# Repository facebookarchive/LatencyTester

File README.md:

Latency Tester
==============

Firmware, Schematics, and Mechanicals for the Oculus Latency Tester.

https://www.oculusvr.com/order/latency-tester/

Firmware
--------

The Latency Tester firmware uses the CooCox CoIDE for development along with 
the gcc-arm-embedded toolchain.

The ST-Link/V2 is the cheapest way to load firmware onto a Latency Tester
board, though any SWD compatible programmer should work.  You can follow these steps
to set up a build environment and load firmware onto the board:

1. Install ST-Link drivers if you haven't: http://www.st.com/web/en/catalog/tools/PF258167
2. Install CoCenter: http://www.coocox.org/CooCox_CoIDE.htm
3. Through CoCenter, install CooCox and CoFlash
4. Install gcc-arm-embedded: https://launchpad.net/gcc-arm-embedded/+download
5. Set up gcc-arm-embedded in CooCox: http://www.coocox.org/CoIDE/Compiler_Settings.html
6. Clone our LatencyTester repository to C:\CooCox\CoIDE\workspace
7. Open the LatencyTester.coproj
8. Build
9. Plug the ST-Link into the board's 10 pin SWD header.
10. Plug in USB to power the board.
12. Download code to Flash 
13. Enjoy!

Note that the USB Product ID is set to 0x0101, which matches the production
version of the Latency Tester.  If you modify the firmware in a way that
changes the USB interface, please change the Product ID to 0x0100.

Mechanical
----------

The Mechanical folder contains STLs of a version of the Latency Tester housing
that is printable on low cost 3D printers as well as STEP files of the original
injection molded housing.

Schematics
----------

The Schematics folder contains an image of the schematic, as well as Eagle CAD files
of the schematic and board layout.

You can also order PCBs directly from OSH Park:

* Main PCB: http://oshpark.com/shared_projects/SHWtp0zm
* Sensor PCB: http://oshpark.com/shared_projects/nyOrdIp9

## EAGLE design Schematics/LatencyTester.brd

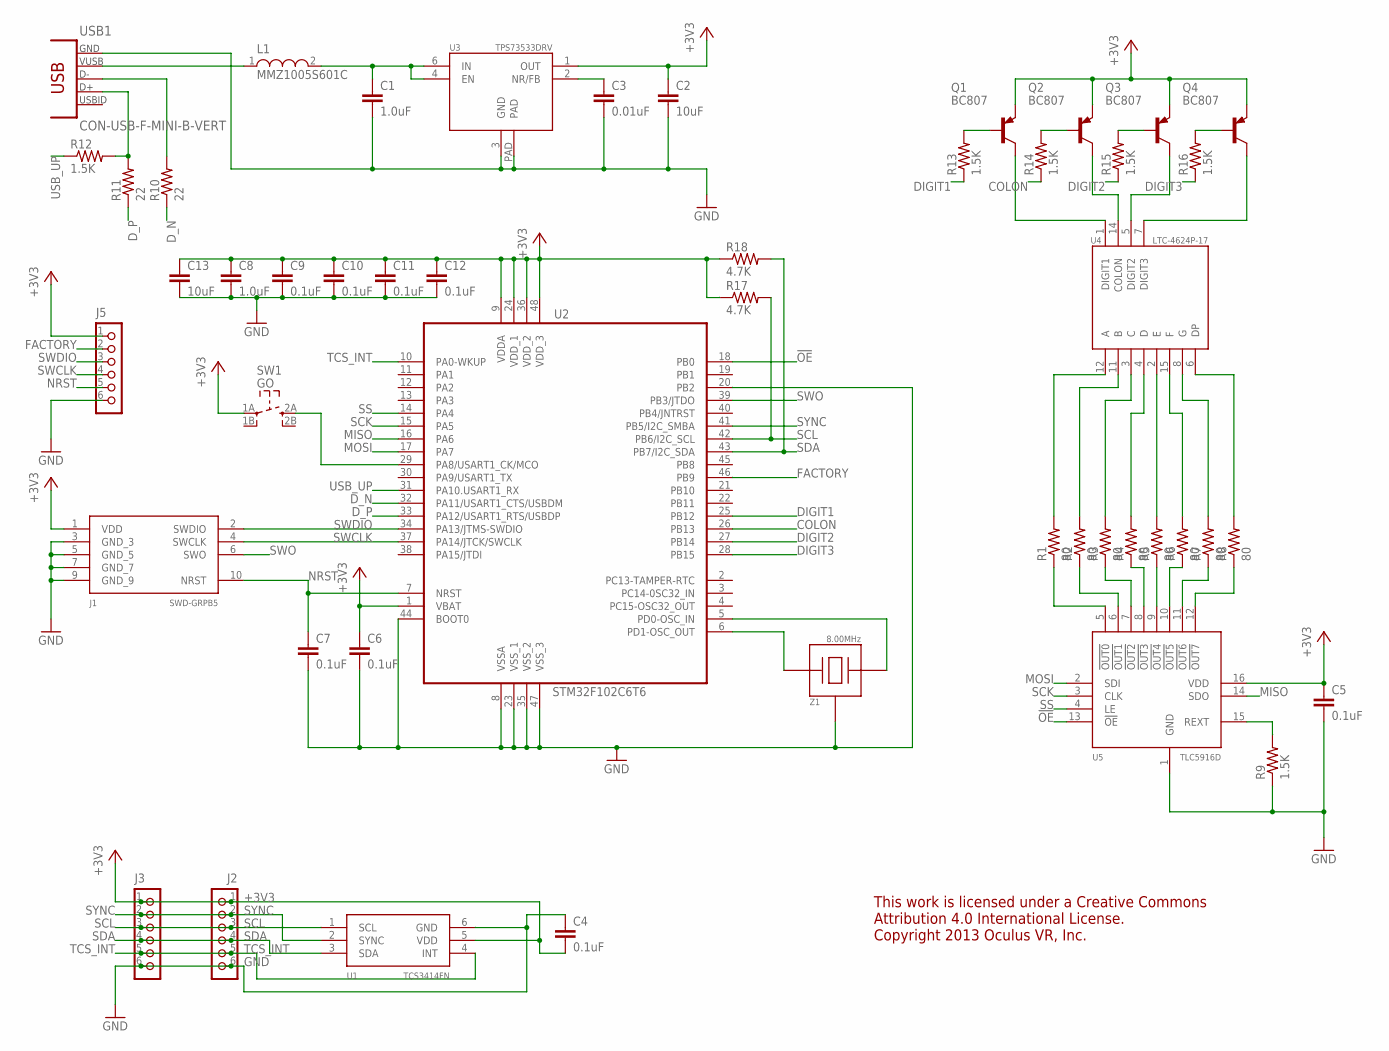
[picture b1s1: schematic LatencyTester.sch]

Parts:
C1, C8: 1.0uF; C0402
C2, C13: 10uF; C0805
C3: 0.01uF; C0402
C4, C5, C6, C7, C9, C10, C11, C12: 0.1uF; C0402
J1: SWD-GRPB5; GRPB5
J2, J3, J5: CON_HEADER_1X06-PTH; M1X6
L1: MMZ1005S601C; C402
Q1, Q2, Q3, Q4: BC807; SOT-323
R1, R2, R3, R4, R5, R6, R7, R8: 80; R0402
R9, R12, R13, R14, R15, R16: 1.5K; R0402
R10, R11: 22; R0402
R17, R18: 4.7K; R0402
SW1: GO; ADTS2
U1: TCS3414FN
U2: STM32F102C6T6; LQFP48
U3: TPS73533DRV; SON-6
U4: LTC-4624P-17; LTC-4624
U5: TLC5916D; SOIC-16
USB1: CON-USB-F-MINI-B-VERT; 651005136421
Z1: 8.00MHz; PQRV

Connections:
!OE: U2.18 (PB0), U5.13 (!OE)
+3V3: C2.1, C4.2, C5.1, C6.1, C8.1, C9.1, C10.1, C11.1, C12.1, C13.1, J1.1 (VDD), J2.1, J3.1, J5.1, Q1.2 (E), Q2.2 (E), Q3.2 (E), Q4.2 (E), R17.1, R18.1, SW1.1A (1), U1.5 (VDD), U2.1 (VBAT), U2.9 (VDDA), U2.24 (VDD_1), U2.36 (VDD_2), U2.48 (VDD_3), U3.1 (OUT), U5.16 (VDD)
COLON: R14.1, U2.26 (PB13)
D1_N: R10.2, USB1.2 (D-)
D1_P: R11.2, R12.2, USB1.3 (D+)
DIGIT1: R13.1, U2.25 (PB12)
DIGIT2: R15.1, U2.27 (PB14)
DIGIT3: R16.1, U2.28 (PB15)
D_N: R10.1, U2.32 (PA11/USART1_CTS/USBDM)
D_P: R11.1, U2.33 (PA12/USART1_RTS/USBDP)
FACTORY: J5.2, U2.46 (PB9)
GND: C1.2, C2.2, C3.2, C4.1, C5.2, C6.2, C7.2, C8.2, C9.2, C10.2, C11.2, C12.2, C13.2, J1.3 (GND_3), J1.5 (GND_5), J1.7 (GND_7), J1.9 (GND_9), J2.6, J3.6, J5.6, R9.1, U1.6 (GND), U2.8 (VSSA), U2.20 (PB2), U2.23 (VSS_1), U2.35 (VSS_2), U2.44 (BOOT0), U2.47 (VSS_3), U3.3 (GND), U3.PAD, U5.1 (GND), USB1.5 (GND), Z1.2 (GND)
MISO: U2.16 (PA6), U5.14 (SDO)
MOSI: U2.17 (PA7), U5.2 (SDI)
unnamed: R1.1, U5.5 (!OUT0)
unnamed: R2.1, U5.6 (!OUT1)
unnamed: R3.1, U5.7 (!OUT2)
unnamed: R4.1, U5.8 (!OUT3)
unnamed: R5.1, U5.9 (!OUT4)
unnamed: R6.1, U5.10 (!OUT5)
unnamed: R7.1, U5.11 (!OUT6)
unnamed: R8.1, U5.12 (!OUT7)
unnamed: R1.2, U4.12 (A)
unnamed: R2.2, U4.11 (B)
unnamed: R3.2, U4.3 (C)
unnamed: R4.2, U4.4 (D)
unnamed: R5.2, U4.2 (E)
unnamed: R6.2, U4.15 (F)
unnamed: R7.2, U4.8 (G)
unnamed: R8.2, U4.6 (DP)
unnamed: U2.6 (PD1-OSC_OUT), Z1.1 (IN)
unnamed: U2.5 (PD0-OSC_IN), Z1.3 (OUT)
unnamed: Q1.3 (C), U4.1 (DIGIT1)
unnamed: Q2.3 (C), U4.14 (COLON)
unnamed: Q3.3 (C), U4.5 (DIGIT2)
unnamed: Q4.3 (C), U4.7 (DIGIT3)
unnamed: SW1.2A (3), U2.29 (PA8/USART1_CK/MCO)
unnamed: C3.1, U3.2 (NR/FB)
unnamed: R9.2, U5.15 (REXT)
unnamed: Q1.1 (B), R13.2
unnamed: Q2.1 (B), R14.2
unnamed: Q3.1 (B), R15.2
unnamed: Q4.1 (B), R16.2
NRST: C7.1, J1.10 (NRST), J5.5, U2.7 (NRST)
SCK: U2.15 (PA5), U5.3 (CLK)
SCL: J2.3, J3.3, R17.2, U1.1 (SCL), U2.42 (PB6/I2C_SCL)
SDA: J2.4, J3.4, R18.2, U1.3 (SDA), U2.43 (PB7/I2C_SDA)
SS: U2.14 (PA4), U5.4 (LE)
SWCLK: J1.4 (SWCLK), J5.4, U2.37 (PA14/JTCK/SWCLK)
SWDIO: J1.2 (SWDIO), J5.3, U2.34 (PA13/JTMS-SWDIO)
SWO: J1.6 (SWO), U2.39 (PB3/JTDO)
SYNC: J2.2, J3.2, U1.2 (SYNC), U2.41 (PB5/I2C_SMBA)
TCS_INT: J2.5, J3.5, U1.4 (INT), U2.10 (PA0-WKUP)
USB_UP: R12.1, U2.31 (PA10.USART1_RX)
VUSB: L1.1, USB1.1 (VUSB)
VUSB_FILTERED: C1.1, L1.2, U3.4 (EN), U3.6 (IN)

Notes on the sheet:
This work is licensed under a Creative Commons Attribution 4.0 International License. Copyright 2013 Oculus VR, Inc.

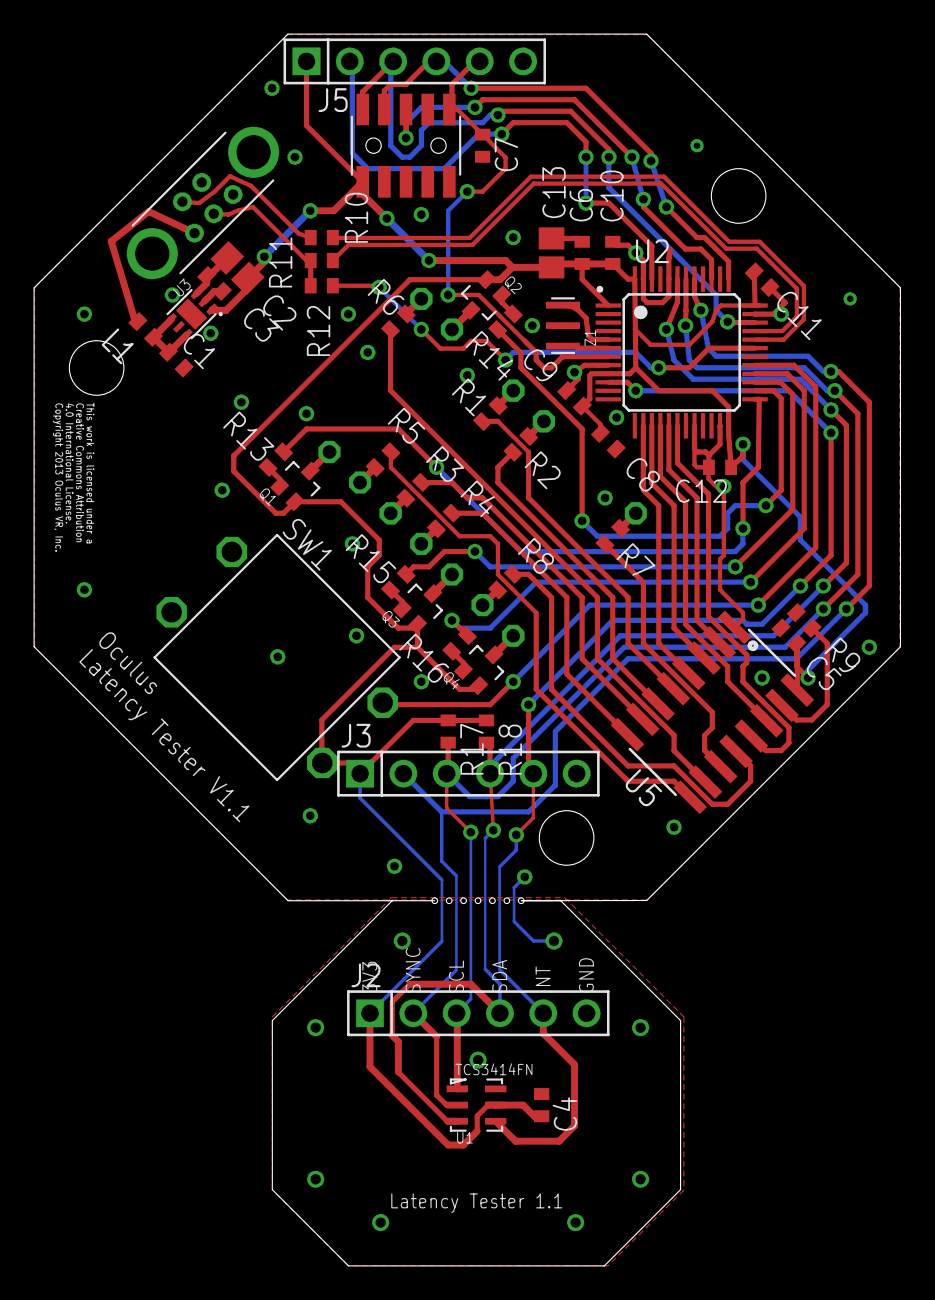
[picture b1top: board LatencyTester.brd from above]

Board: 2 copper layers, 50.8 x 72.2 mm, 51 parts (0 on the bottom side), 56 nets.

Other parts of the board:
U$1, U$2, U$3: HOLE_3.2

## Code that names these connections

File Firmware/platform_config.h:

/*****************************************************************************

Filename    :   platform_config.h
Content     :   Pin definitions for the Latency Tester
Created     :
Authors     :   Nirav Patel
Copyright   :   Copyright 2013 Oculus VR, Inc. All Rights reserved.

Licensed under the Apache License, Version 2.0 (the "License");
you may not use this file except in compliance with the License.
You may obtain a copy of the License at

http://www.apache.org/licenses/LICENSE-2.0

Unless required by applicable law or agreed to in writing, software
distributed under the License is distributed on an "AS IS" BASIS,
WITHOUT WARRANTIES OR CONDITIONS OF ANY KIND, either express or implied.
See the License for the specific language governing permissions and
limitations under the License.

*****************************************************************************/

#ifndef _PLATFORM_CONFIG_H_
#define _PLATFORM_CONFIG_H_

#if defined(STM32L1XX_MD) || defined(STM32L1XX_HD)|| defined(STM32L1XX_MD_PLUS)
  #include "stm32l1xx.h"
#elif defined (STM32F10X_LD) || defined (STM32F10X_MD) || defined (STM32F10X_HD) || defined (STM32F10X_XL) || defined (STM32F10X_CL)
  #include "stm32f10x.h"
#endif

/* Define the STM32F10x hardware depending on the used evaluation board */
#if defined (USE_TRACKER_V1)

  #define USB_DISCONNECT                      GPIOA
  #define USB_DISCONNECT_PIN                  GPIO_Pin_2
  #define RCC_APB2Periph_GPIO_DISCONNECT      RCC_APB2Periph_GPIOA

#ifdef USE_AVAGO
  #define RED_PORT                            GPIOB
  #define RED_PIN                             GPIO_Pin_0
  #define RED_RCC                             RCC_APB2Periph_GPIOB
  #define RED_CHANNEL                         ADC_Channel_8
  #define GREEN_PORT                          GPIOB
  #define GREEN_PIN                           GPIO_Pin_1
  #define GREEN_RCC                           RCC_APB2Periph_GPIOB
  #define GREEN_CHANNEL                       ADC_Channel_9
  #define BLUE_PORT                           GPIOA
  #define BLUE_PIN                            GPIO_Pin_3
  #define BLUE_RCC                            RCC_APB2Periph_GPIOA
  #define BLUE_CHANNEL                        ADC_Channel_3
  #define BUTTON_PORT                         GPIOB
  #define BUTTON_PIN                          GPIO_Pin_10
  #define BUTTON_RCC                          RCC_APB2Periph_GPIOB
#else
  #define TCS_I2C                             I2C2
  #define TCS_I2C_RCC                         RCC_APB1Periph_I2C2
  #define TCS_SCL_PIN                         GPIO_Pin_10
  #define TCS_SDA_PIN                         GPIO_Pin_11
  #define TCS_SCL_SDA_PORT                    GPIOB
  #define TCS_SCL_SDA_RCC                     RCC_APB2Periph_GPIOB
  #define TCS_SYNC_PIN                        GPIO_Pin_5
  #define TCS_SYNC_PORT                       GPIOB
  #define TCS_SYNC_RCC                        RCC_APB2Periph_GPIOB
  #define BUTTON_PORT                         GPIOB
  #define BUTTON_PIN                          GPIO_Pin_0
  #define BUTTON_RCC                          RCC_APB2Periph_GPIOB
#endif /* USE_AVAGO */

#elif defined (USE_LATENCY_TESTER)

  #define USB_DISCONNECT                      GPIOA
  #define USB_DISCONNECT_PIN                  GPIO_Pin_10
  #define RCC_APB2Periph_GPIO_DISCONNECT      RCC_APB2Periph_GPIOA

  #define TCS_I2C                             I2C1
  #define TCS_I2C_RCC                         RCC_APB1Periph_I2C1
  #define TCS_SCL_PIN                         GPIO_Pin_6
  #define TCS_SDA_PIN                         GPIO_Pin_7
  #define TCS_SCL_SDA_PORT                    GPIOB
  #define TCS_SCL_SDA_RCC                     RCC_APB2Periph_GPIOB
  #define TCS_SYNC_PIN                        GPIO_Pin_5
  #define TCS_SYNC_PORT                       GPIOB
  #define TCS_SYNC_RCC                        RCC_APB2Periph_GPIOB

  #define BUTTON_PORT                         GPIOA
  #define BUTTON_PIN                          GPIO_Pin_8
  #define BUTTON_RCC                          RCC_APB2Periph_GPIOA

  #define FACTORY_PIN                         GPIO_Pin_9
  #define FACTORY_PORT                        GPIOB
  #define FACTORY_RCC                         RCC_APB2Periph_GPIOB

#ifdef USE_7_SEG
  #define TLC_SPI                             SPI1
  #define TLC_SPI_RCC                         RCC_APB2Periph_SPI1
  #define TLC_SPI_PRESCALER                   SPI_BaudRatePrescaler_4
  #define TLC_SS_PIN                          GPIO_Pin_4
  #define TLC_SS_PORT                         GPIOA
  #define TLC_SS_RCC                          RCC_APB2Periph_GPIOA
  #define TLC_SCK_PIN                         GPIO_Pin_5
  #define TLC_MISO_PIN                        GPIO_Pin_6
  #define TLC_MOSI_PIN                        GPIO_Pin_7
  #define TLC_SCK_MISO_MOSI_PORT              GPIOA
  #define TLC_SCK_MISO_MOSI_RCC               RCC_APB2Periph_GPIOA
  #define TLC_OE_PIN                          GPIO_Pin_0
  #define TLC_OE_PORT                         GPIOB
  #define TLC_OE_RCC                          RCC_APB2Periph_GPIOB

  #define DIGIT1_PIN                          GPIO_Pin_12
  #define DIGIT1_PORT                         GPIOB
  #define DIGIT1_RCC                          RCC_APB2Periph_GPIOB
  #define COLON_PIN                           GPIO_Pin_13
  #define COLON_PORT                          GPIOB
  #define COLON_RCC                           RCC_APB2Periph_GPIOB
  #define DIGIT2_PIN                          GPIO_Pin_14
  #define DIGIT2_PORT                         GPIOB
  #define DIGIT2_RCC                          RCC_APB2Periph_GPIOB
  #define DIGIT3_PIN                          GPIO_Pin_15
  #define DIGIT3_PORT                         GPIOB
  #define DIGIT3_RCC                          RCC_APB2Periph_GPIOB
#endif /* USE_7_SEG */

#endif /* USE_TRACKER_V1 */

#endif /* _PLATFORM_CONFIG_H_ */

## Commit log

2013-12-15 Initial untested port of LatencyTester firmware
    Porting to use CooCox and gcc-arm-embedded.
    Also add Apache license headers to our files.
2013-12-15 Latency Tester Schematic
2013-12-16 Fix the vector table, since we're not bootloaded
2013-12-16 Added latency tester STLs
2013-12-16 Add an image to the Readme
2013-12-16 Top fits PCB better, now buttonless design
2013-12-16 Add Eagle files of the board
2013-12-17 No more PCB spacer, minor tweaks to top
2013-12-22 Add interface specification and BOM
2014-01-03 USB Product ID info in the Readme
2014-02-05 Add development environment setup instructions
2014-02-05 Add OSH Park PCB urls
2014-02-05 STEP files for the injection molded housing
2014-02-05 Mention the injection molded housing model
